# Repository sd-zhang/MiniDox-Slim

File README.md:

# MiniDox-Slim

Repository contains Eagle and STL files for MiniDox-Slim.

Original MiniDox is created by u/That-Canadian on reddit, and can be found here:
https://github.com/That-Canadian/MiniDox_PCB

To make your own:
Keypad PCB MUST be 0.6mm thick or thinner. Control board PCB MUST be 1.6mm thick.

Recommended parts:
- Diode: https://www.digikey.ca/product-detail/en/micro-commercial-co/1N4148W-TP/1N4148WTPMSCT-ND/717311
- TRRRS Jack: https://www.digikey.ca/product-detail/en/cui-devices/SJ-43614-SMT-TR/CP-43614SJCT-ND/2625179
TRRRS Jack will need slight trimming to fit.

Assembly instructions will be posted after second set is build. Whenever that may be.

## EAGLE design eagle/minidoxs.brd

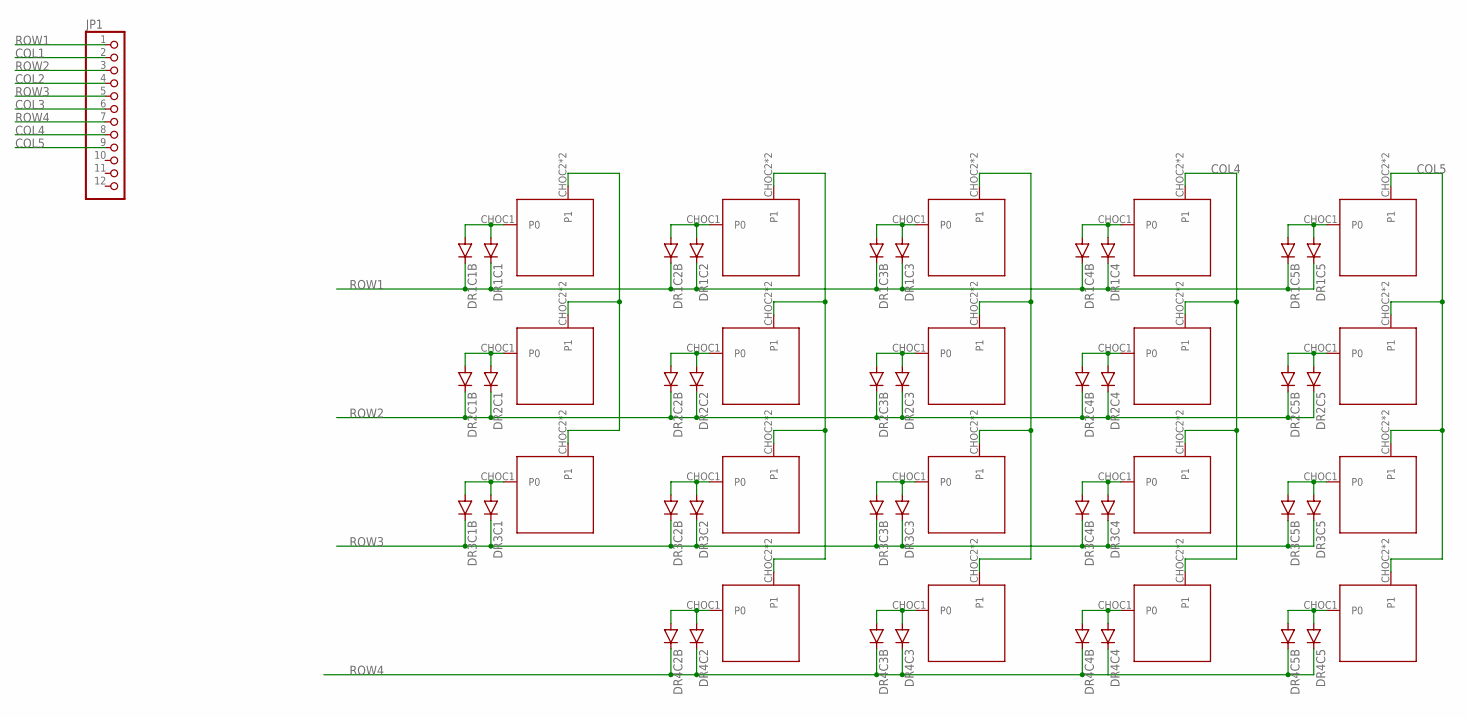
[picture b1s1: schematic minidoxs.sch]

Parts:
DR1C1, DR1C1B, DR1C2, DR1C2B, DR1C3, DR1C3B, DR1C4, DR1C4B, DR1C5, DR1C5B, DR2C1, DR2C1B, DR2C2, DR2C2B, DR2C3, DR2C3B, DR2C4, DR2C4B, DR2C5, DR2C5B, DR3C1, DR3C1B, DR3C2, DR3C2B, DR3C3, DR3C3B, DR3C4, DR3C4B, DR3C5, DR3C5B, DR4C2, DR4C2B, DR4C3, DR4C3B, DR4C4, DR4C4B, DR4C5, DR4C5B: MBR0520LT; SOD123
JP1: PINHD-1X12; 1X12
U$R1C1, U$R1C2, U$R1C3, U$R1C4, U$R1C5, U$R2C1, U$R2C2, U$R2C3, U$R2C4, U$R2C5, U$R3C1, U$R3C2, U$R3C3, U$R3C4, U$R3C5, U$R4C2, U$R4C3, U$R4C4, U$R4C5: KEYSWITCH-PLAIN-CHOC-1U; CHOC-1U

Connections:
COL1: JP1.2, U$R1C1.CHOC2 (P1), U$R1C1.CHOC3 (P1), U$R2C1.CHOC2 (P1), U$R2C1.CHOC3 (P1), U$R3C1.CHOC2 (P1), U$R3C1.CHOC3 (P1)
COL2: JP1.4, U$R1C2.CHOC2 (P1), U$R1C2.CHOC3 (P1), U$R2C2.CHOC2 (P1), U$R2C2.CHOC3 (P1), U$R3C2.CHOC2 (P1), U$R3C2.CHOC3 (P1), U$R4C2.CHOC2 (P1), U$R4C2.CHOC3 (P1)
COL3: JP1.6, U$R1C3.CHOC2 (P1), U$R1C3.CHOC3 (P1), U$R2C3.CHOC2 (P1), U$R2C3.CHOC3 (P1), U$R3C3.CHOC2 (P1), U$R3C3.CHOC3 (P1), U$R4C3.CHOC2 (P1), U$R4C3.CHOC3 (P1)
COL4: JP1.8, U$R1C4.CHOC2 (P1), U$R1C4.CHOC3 (P1), U$R2C4.CHOC2 (P1), U$R2C4.CHOC3 (P1), U$R3C4.CHOC2 (P1), U$R3C4.CHOC3 (P1), U$R4C4.CHOC2 (P1), U$R4C4.CHOC3 (P1)
COL5: JP1.9, U$R1C5.CHOC2 (P1), U$R1C5.CHOC3 (P1), U$R2C5.CHOC2 (P1), U$R2C5.CHOC3 (P1), U$R3C5.CHOC2 (P1), U$R3C5.CHOC3 (P1), U$R4C5.CHOC2 (P1), U$R4C5.CHOC3 (P1)
unnamed: DR1C1.A, DR1C1B.A, U$R1C1.CHOC1 (P0)
unnamed: DR2C1.A, DR2C1B.A, U$R2C1.CHOC1 (P0)
unnamed: DR1C5.A, DR1C5B.A, U$R1C5.CHOC1 (P0)
unnamed: DR1C4.A, DR1C4B.A, U$R1C4.CHOC1 (P0)
unnamed: DR1C3.A, DR1C3B.A, U$R1C3.CHOC1 (P0)
unnamed: DR2C2.A, DR2C2B.A, U$R2C2.CHOC1 (P0)
unnamed: DR2C3.A, DR2C3B.A, U$R2C3.CHOC1 (P0)
unnamed: DR2C4.A, DR2C4B.A, U$R2C4.CHOC1 (P0)
unnamed: DR1C2.A, DR1C2B.A, U$R1C2.CHOC1 (P0)
unnamed: DR2C5.A, DR2C5B.A, U$R2C5.CHOC1 (P0)
unnamed: DR3C4.A, DR3C4B.A, U$R3C4.CHOC1 (P0)
unnamed: DR3C3.A, DR3C3B.A, U$R3C3.CHOC1 (P0)
unnamed: DR3C2.A, DR3C2B.A, U$R3C2.CHOC1 (P0)
unnamed: DR3C1.A, DR3C1B.A, U$R3C1.CHOC1 (P0)
unnamed: DR3C5.A, DR3C5B.A, U$R3C5.CHOC1 (P0)
unnamed: DR4C4.A, DR4C4B.A, U$R4C4.CHOC1 (P0)
unnamed: DR4C3.A, DR4C3B.A, U$R4C3.CHOC1 (P0)
unnamed: DR4C2.A, DR4C2B.A, U$R4C2.CHOC1 (P0)
unnamed: DR4C5.A, DR4C5B.A, U$R4C5.CHOC1 (P0)
ROW1: DR1C1.C, DR1C1B.C, DR1C2.C, DR1C2B.C, DR1C3.C, DR1C3B.C, DR1C4.C, DR1C4B.C, DR1C5.C, DR1C5B.C, JP1.1
ROW2: DR2C1.C, DR2C1B.C, DR2C2.C, DR2C2B.C, DR2C3.C, DR2C3B.C, DR2C4.C, DR2C4B.C, DR2C5.C, DR2C5B.C, JP1.3
ROW3: DR3C1.C, DR3C1B.C, DR3C2.C, DR3C2B.C, DR3C3.C, DR3C3B.C, DR3C4.C, DR3C4B.C, DR3C5.C, DR3C5B.C, JP1.5
ROW4: DR4C2.C, DR4C2B.C, DR4C3.C, DR4C3B.C, DR4C4.C, DR4C4B.C, DR4C5.C, DR4C5B.C, JP1.7

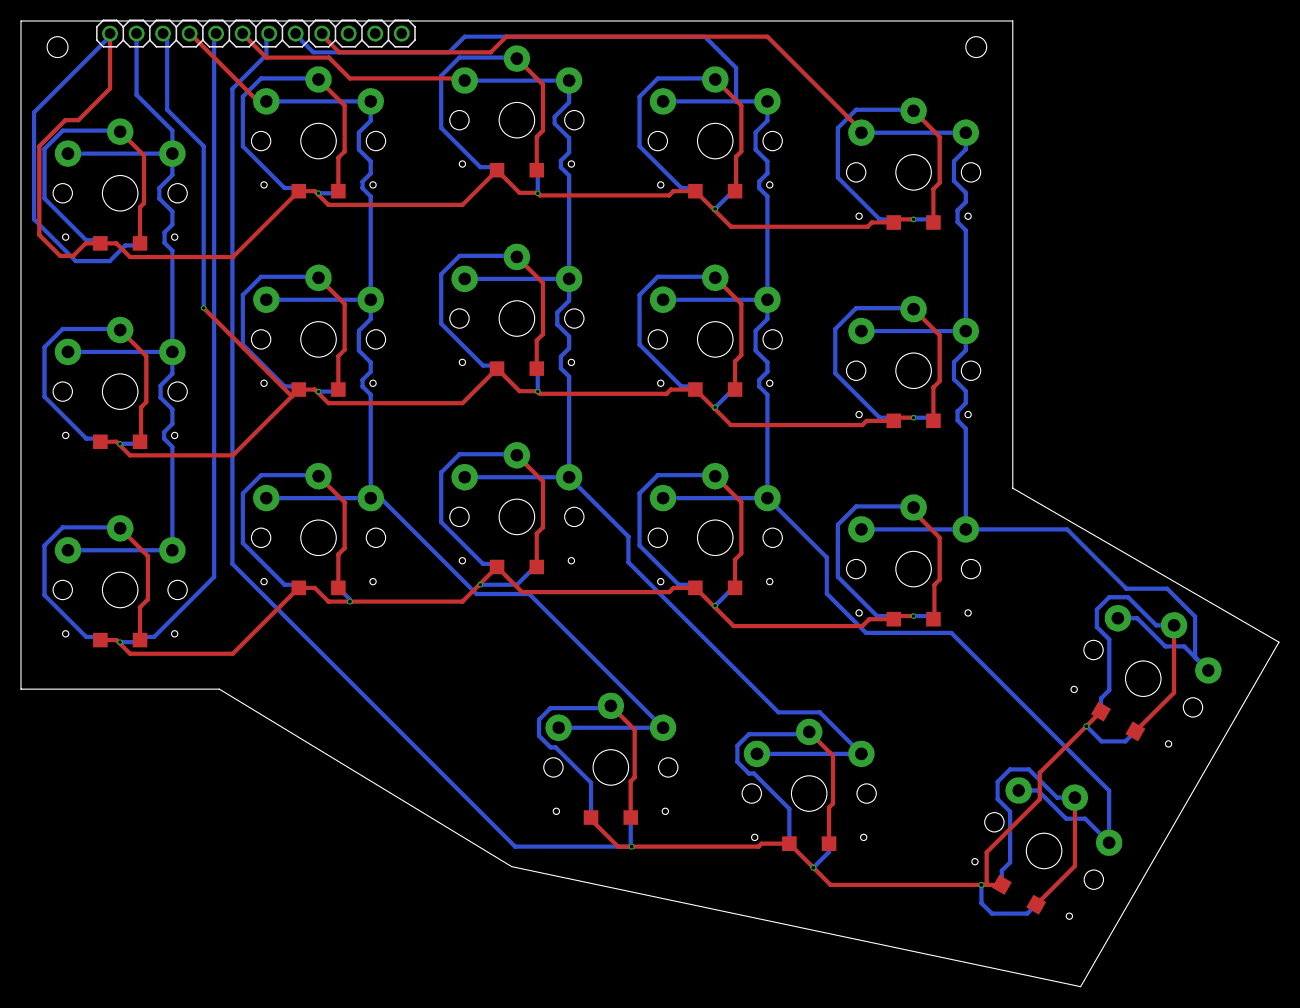
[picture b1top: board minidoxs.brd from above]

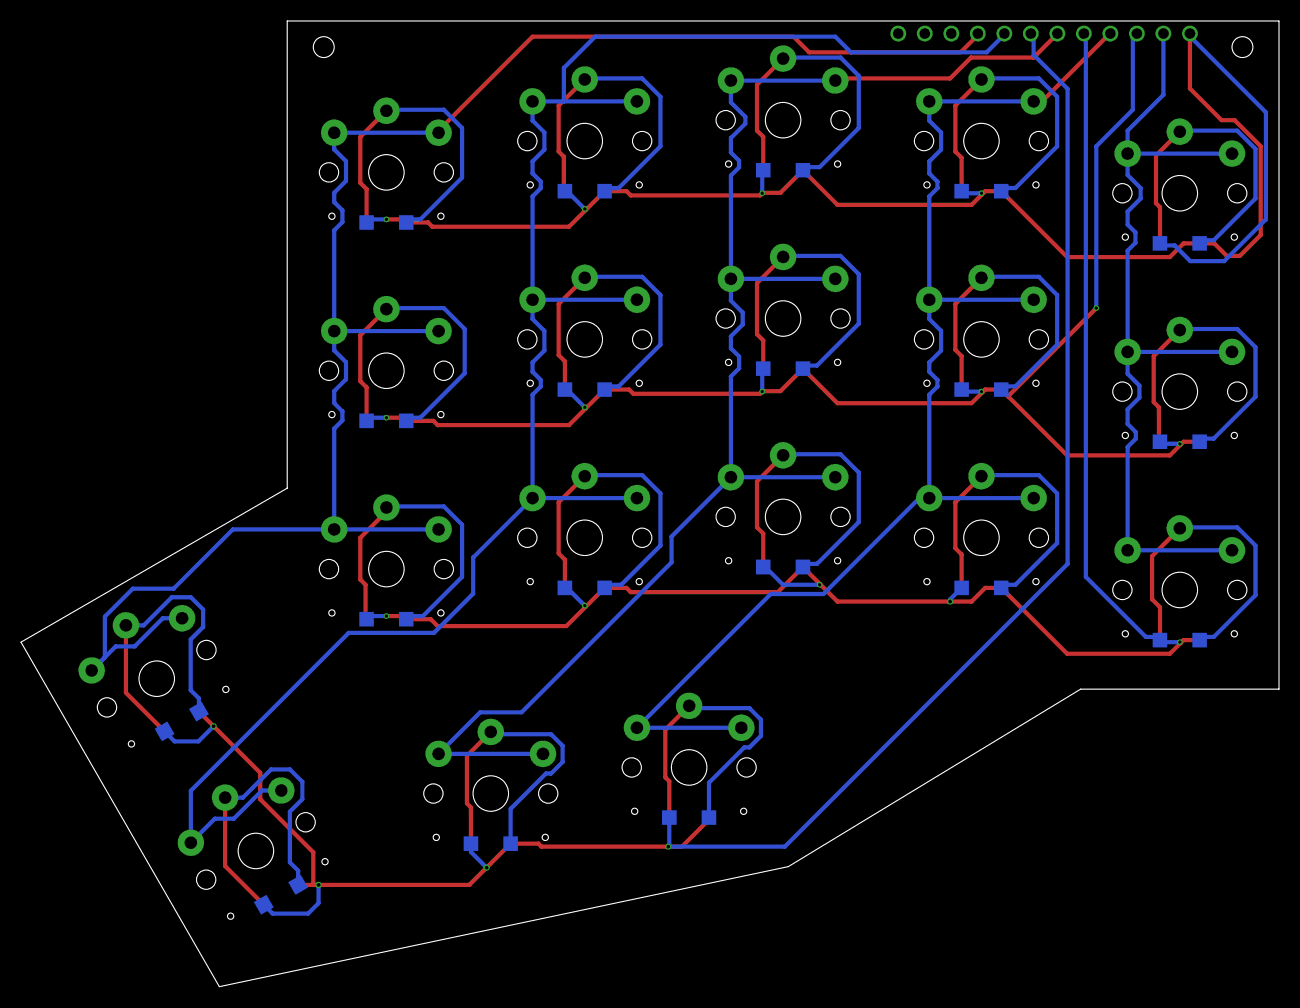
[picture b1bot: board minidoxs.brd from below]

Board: 2 copper layers, 120.5 x 92.5 mm, 58 parts (19 on the bottom side), 28 nets.

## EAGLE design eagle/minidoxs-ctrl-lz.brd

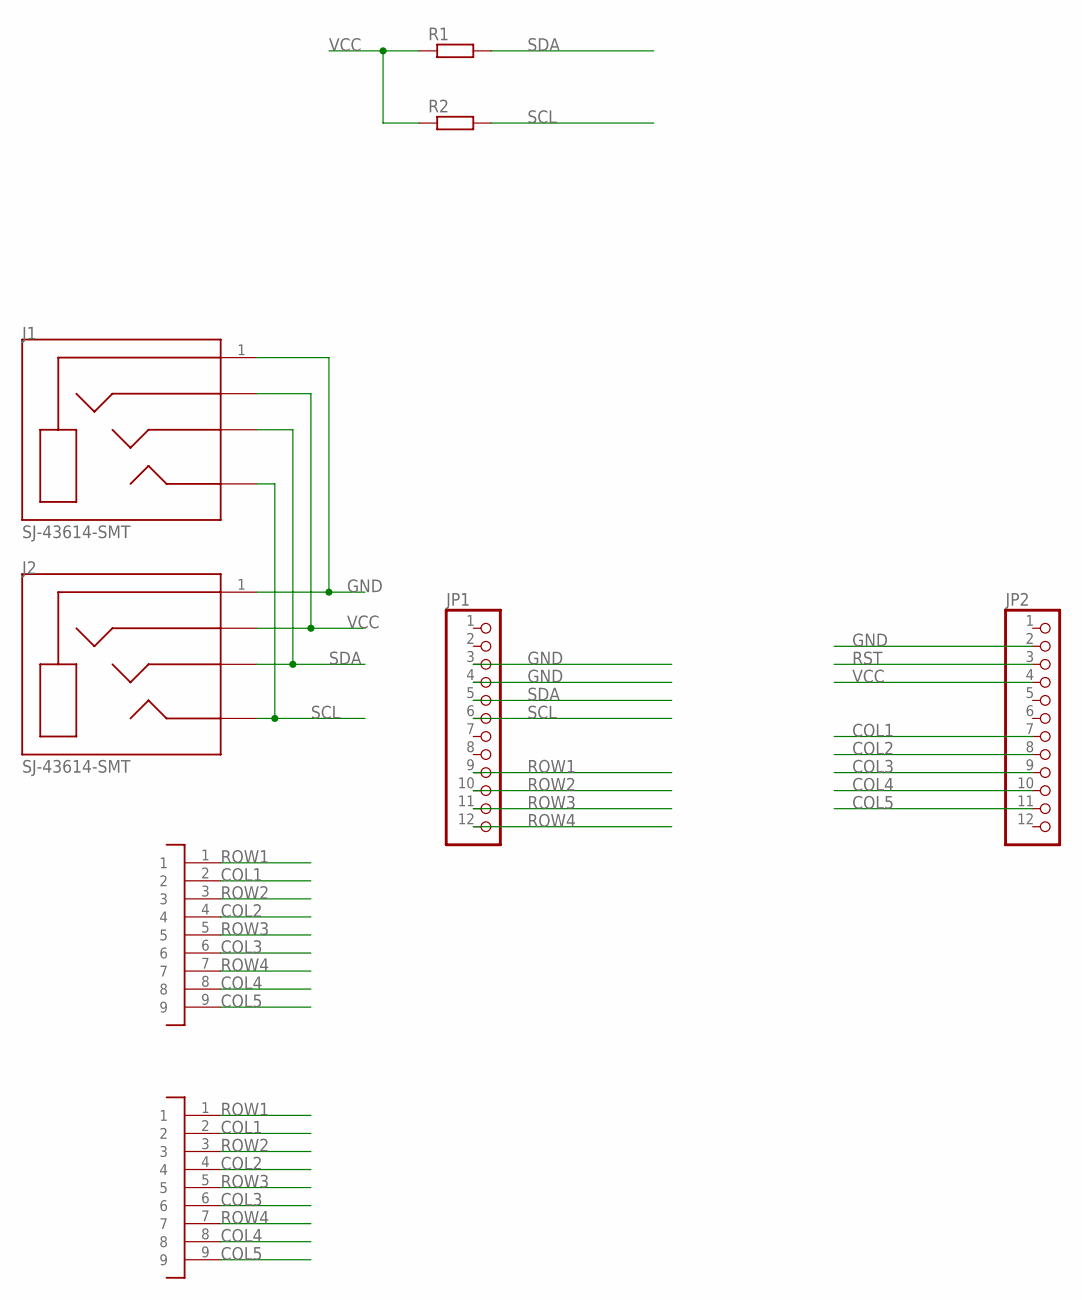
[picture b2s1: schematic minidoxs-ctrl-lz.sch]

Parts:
J1, J2: SJ-43614-SMT; CUI_SJ-43614-SMT
JP1, JP2: PINHD-1X12; 1X12
R1, R2: RESISTOR-0603; R0603
U$1, U$2: HEADER-9X1-2.54

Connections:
COL1: JP2.7, U$1.2, U$2.2
COL2: JP2.8, U$1.4, U$2.4
COL3: JP2.9, U$1.6, U$2.6
COL4: JP2.10, U$1.8, U$2.8
COL5: JP2.11, U$1.9, U$2.9
GND: J1.1 (SLEEVE), J2.1 (SLEEVE), JP1.3, JP1.4, JP2.2
ROW1: JP1.9, U$1.1, U$2.1
ROW2: JP1.10, U$1.3, U$2.3
ROW3: JP1.11, U$1.5, U$2.5
ROW4: JP1.12, U$1.7, U$2.7
RST: JP2.3
SCL: J1.2 (TIP), J2.2 (TIP), JP1.6, R2.2
SDA: J1.3 (RING1), J2.3 (RING1), JP1.5, R1.2
VCC: J1.4 (RING2), J2.4 (RING2), JP2.4, R1.1, R2.1

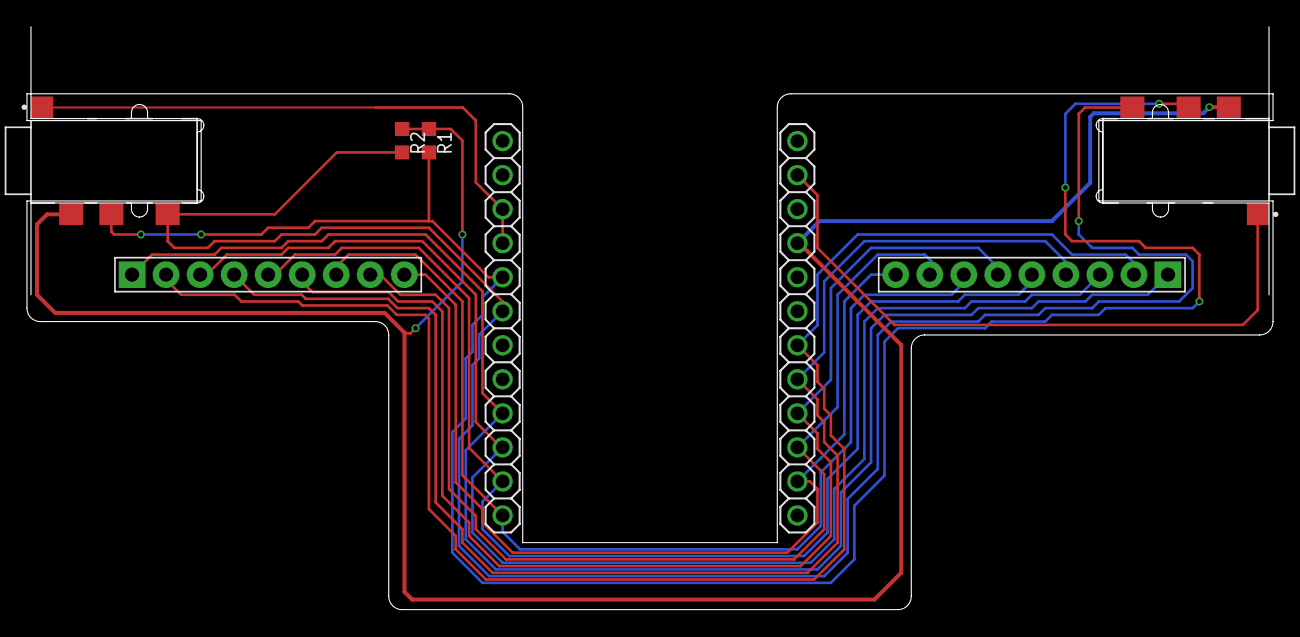
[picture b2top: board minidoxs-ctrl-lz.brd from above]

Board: 2 copper layers, 93.0 x 43.5 mm, 8 parts (0 on the bottom side), 13 nets.
